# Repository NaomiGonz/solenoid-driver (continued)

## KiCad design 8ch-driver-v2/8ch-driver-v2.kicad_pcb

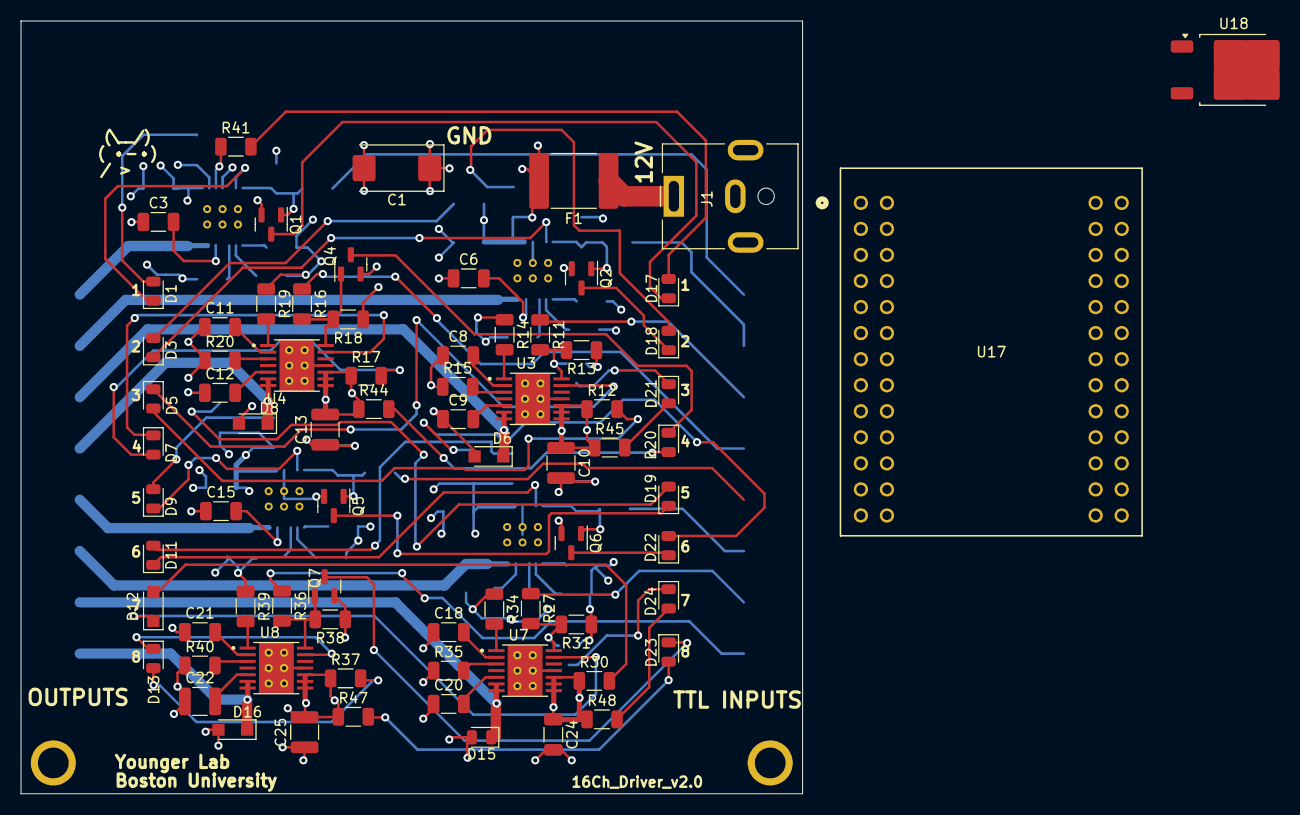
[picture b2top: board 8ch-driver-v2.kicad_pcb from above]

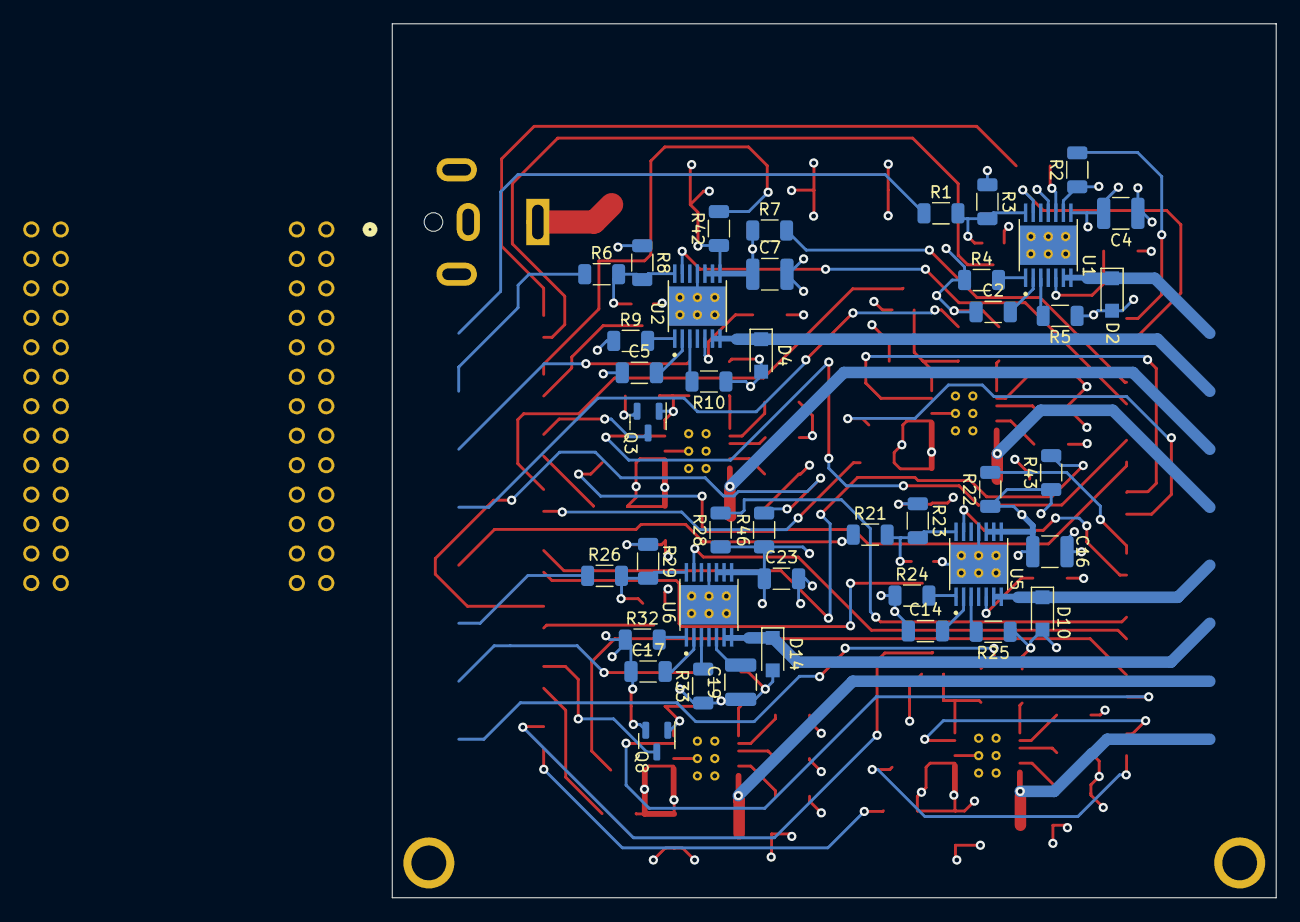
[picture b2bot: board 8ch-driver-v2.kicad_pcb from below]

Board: 4 copper layers, 76.2 x 75.3 mm, 119 parts (42 on the bottom side), 91 nets.

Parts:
C1: 47uF; CP_EIA-7343-43_Kemet-X_Pad2.25x2.55mm_HandSolder
C2, C5, C8, C11, C14, C17, C20, C23: 0.18uF; C_1206_3216Metric
C3, C6, C9, C12, C15, C18, C21, C24: 470pF; C_1206_3216Metric
C4, C7, C10, C13, C16, C19, C22, C25: 10uF; C_1210_3225Metric
D1, D3, D5, D7, D9, D11, D13, D15: LED; LED_0805_2012Metric
D2, D4, D6, D8, D10, D12, D14, D16: PMEG10010ELRX; Nexperia_CFP3_SOD-123W
D17, D18, D19, D20, D21, D22, D23, D24: LED Green; LED_0805_2012Metric
F1: 0ZCF0125FF2C; Fuse_2920_7451Metric
H1, H2: MountingHole; MountingHole_2.2mm_M2_Pad
J1: Barrel_Jack; BarrelJack_CUI_PJ-063AH_Horizontal
Q1, Q2, Q3, Q4, Q5, Q6, Q7, Q8: 2N7002E; SOT-23
R1, R6, R11, R16, R21, R26, R31, R36: 49R9; R_1206_3216Metric
R2, R3, R7, R8, R12, R13, R17, R18, R22, R23, R27, R28, R32, R33, R37, R38: 4k7; R_1206_3216Metric
R4, R9, R14, R19, R24, R29, R34, R39: 162k; R_1206_3216Metric
R5, R10, R15, R20, R25, R30, R35, R40: 191k; R_1206_3216Metric
R41, R42, R43, R44, R45, R46, R47, R48: 10K; R_1206_3216Metric
U1, U2, U3, U4, U5, U6, U7, U8: DRV104PWP; IC_TPS27S100BPWPR
U17: FT4232H MINI MODULE; FT4232H_FTD
U18: BD33FC0FP; TO-252-2

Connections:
+3.3V: U17.CN2-1 (V3V3), U17.CN2-3 (V3V3), U17.CN2-5 (V3V3), U18.3 (VO)
+12V: C1.1, C4.1, C7.1, C10.1, C13.1, C16.1, C19.1, C22.1, C25.1, F1.2, R2.1, R7.1, R12.1, R17.1, R22.1, R27.1, R32.1, R37.1, R41.1, R42.1, R43.1, R44.1, R45.1, R46.1, R47.1, R48.1, U1.8 (VPS2), U1.9 (VPS1), U1.10 (+VS), U2.8 (VPS2), U2.9 (VPS1), U2.10 (+VS), U3.8 (VPS2), U3.9 (VPS1), U3.10 (+VS), U4.8 (VPS2), U4.9 (VPS1), U4.10 (+VS), U5.8 (VPS2), U5.9 (VPS1), U5.10 (+VS), U6.8 (VPS2), U6.9 (VPS1), U6.10 (+VS), U7.8 (VPS2), U7.9 (VPS1), U7.10 (+VS), U8.8 (VPS2), U8.9 (VPS1), U8.10 (+VS), U18.1 (VCC)
/12V_IN: F1.1, J1.1
/additonal-channels-p1/delay3: C8.2, U3.2 (DELAY_ADJ)
/additonal-channels-p1/delay4: C11.2, U4.2 (DELAY_ADJ)
/additonal-channels-p1/delay5: C14.2, U5.2 (DELAY_ADJ)
/additonal-channels-p1/duty3: R14.2, U3.1 (DUTY_CYCLE_ADJ)
/additonal-channels-p1/duty4: R19.2, U4.1 (DUTY_CYCLE_ADJ)
/additonal-channels-p1/duty5: R24.2, U5.1 (DUTY_CYCLE_ADJ)
/additonal-channels-p1/fault3: D5.1 (K), U3.13 (STATUS_OK_FLAG)
/additonal-channels-p1/fault4: D7.1 (K), U4.13 (STATUS_OK_FLAG)
/additonal-channels-p1/fault5: D9.1 (K), U5.13 (STATUS_OK_FLAG)
/additonal-channels-p1/freq3: R15.2, U3.3 (OSC_FREQ_ADJ)
/additonal-channels-p1/freq4: R20.2, U4.3 (OSC_FREQ_ADJ)
/additonal-channels-p1/freq5: R25.2, U5.3 (OSC_FREQ_ADJ)
/additonal-channels-p1/in_term3: Q3.1 (G), R11.2, R13.2, U3.14 (INPUT)
/additonal-channels-p1/in_term4: Q4.1 (G), R16.2, R18.2, U4.14 (INPUT)
/additonal-channels-p1/in_term5: Q5.1 (G), R21.2, R23.2, U5.14 (INPUT)
/additonal-channels-p2/delay6: C17.2, U6.2 (DELAY_ADJ)
/additonal-channels-p2/delay7: C20.2, U7.2 (DELAY_ADJ)
/additonal-channels-p2/delay8: C23.2, U8.2 (DELAY_ADJ)
/additonal-channels-p2/duty6: R29.2, U6.1 (DUTY_CYCLE_ADJ)
/additonal-channels-p2/duty7: R34.2, U7.1 (DUTY_CYCLE_ADJ)
/additonal-channels-p2/duty8: R39.2, U8.1 (DUTY_CYCLE_ADJ)
/additonal-channels-p2/fault6: D11.1 (K), U6.13 (STATUS_OK_FLAG)
/additonal-channels-p2/fault7: D13.1 (K), U7.13 (STATUS_OK_FLAG)
/additonal-channels-p2/fault8: D15.1 (K), U8.13 (STATUS_OK_FLAG)
/additonal-channels-p2/freq6: R30.2, U6.3 (OSC_FREQ_ADJ)
/additonal-channels-p2/freq7: R35.2, U7.3 (OSC_FREQ_ADJ)
/additonal-channels-p2/freq8: R40.2, U8.3 (OSC_FREQ_ADJ)
/additonal-channels-p2/in_term5: R26.2, R28.2, R31.2, R33.2, R36.2, R38.2, U6.14 (INPUT), U7.14 (INPUT), U8.14 (INPUT)
/delay1: C2.2, U1.2 (DELAY_ADJ)
/delay2: C5.2, U2.2 (DELAY_ADJ)
/duty1: R4.2, U1.1 (DUTY_CYCLE_ADJ)
/duty2: R9.2, U2.1 (DUTY_CYCLE_ADJ)
/fault1: D1.1 (K), U1.13 (STATUS_OK_FLAG)
/fault2: D3.1 (K), U2.13 (STATUS_OK_FLAG)
/freq1: R5.2, U1.3 (OSC_FREQ_ADJ)
/freq2: R10.2, U2.3 (OSC_FREQ_ADJ)
/in_term1: Q1.1 (G), R1.2, R3.2, U1.14 (INPUT)
/in_term2: Q2.1 (G), R6.2, R8.2, U2.14 (INPUT)
GND: C1.2, C2.1, C3.1, C4.2, C5.1, C6.1, C7.2, C8.1, C9.1, C10.2, C11.1, C12.1, C13.2, C14.1, C15.1, C16.2, C17.1, C18.1, C19.2, C20.1, C21.1, C22.2, C23.1, C24.1, C25.2, D2.2 (A), D4.2 (A), D6.2 (A), D8.2 (A), D10.2 (A), D12.2 (A), D14.2 (A), D16.2 (A), J1.2, Q1.2 (S), Q2.2 (S), Q3.2 (S), Q4.2 (S), Q5.2 (S), Q6.2 (S), Q7.2 (S), Q8.2 (S), R3.1, R4.1, R5.1, R8.1, R9.1, R10.1, R13.1, R14.1, R15.1, R18.1, R19.1, R20.1, R23.1, R24.1, R25.1, R28.1, R29.1, R30.1, R33.1, R34.1, R35.1, R38.1, R39.1, R40.1, U1.11 (GND), U1.15 (EPAD), U2.11 (GND), U2.15 (EPAD), U3.11 (GND), U3.15 (EPAD), U4.11 (GND), U4.15 (EPAD), U5.11 (GND), U5.15 (EPAD), U6.11 (GND), U6.15 (EPAD), U7.11 (GND), U7.15 (EPAD), U8.11 (GND), U8.15 (EPAD), U17.CN2-2 (GND), U17.CN2-4 (GND), U17.CN2-6 (GND), U18.2 (GND)
unnamed: D1.2 (A), R2.2
unnamed: D3.2 (A), R7.2
unnamed: D5.2 (A), R12.2
unnamed: D7.2 (A), R17.2
unnamed: D9.2 (A), R22.2
unnamed: D11.2 (A), R27.2
unnamed: D13.2 (A), R32.2
unnamed: D15.2 (A), R37.2
unnamed: D17.2 (A), R41.2
unnamed: D17.1 (K), Q1.3 (D)
unnamed: D18.2 (A), R42.2
unnamed: D18.1 (K), Q2.3 (D)
unnamed: D19.2 (A), R43.2
unnamed: D19.1 (K), Q5.3 (D)
unnamed: D20.2 (A), R44.2
unnamed: D20.1 (K), Q4.3 (D)
unnamed: D21.2 (A), R45.2
unnamed: D21.1 (K), Q3.3 (D)
unnamed: D22.2 (A), R46.2
unnamed: D22.1 (K), Q6.3 (D)
unnamed: D23.2 (A), R47.2
unnamed: D23.1 (K), Q8.3 (D)
unnamed: D24.2 (A), R48.2
unnamed: D24.1 (K), Q7.3 (D)
unnamed: C3.2, U1.5 (BOOT)
unnamed: C6.2, U2.5 (BOOT)
unnamed: C9.2, U3.5 (BOOT)
unnamed: C12.2, U4.5 (BOOT)
unnamed: C15.2, U5.5 (BOOT)
unnamed: C18.2, U6.5 (BOOT)
unnamed: C21.2, U7.5 (BOOT)
unnamed: C24.2, U8.5 (BOOT)
unnamed: U17.CN3-1 (VBUS), U17.CN3-3 (VCC)
Relay01: R1.1, U17.CN2-7 (AD0)
Relay02: R6.1, U17.CN2-10 (AD1)
Relay03: R11.1, U17.CN2-9 (AD2)
Relay04: R16.1, U17.CN2-12 (AD3)
Relay05: R21.1, U17.CN2-14 (AD4)
Relay06: R26.1, U17.CN2-13 (AD5)
Relay07: R31.1, U17.CN2-16 (AD6)
Relay08: R36.1, U17.CN2-15 (AD7)
out01: D2.1 (K), U1.6 (OUT1), U1.7 (OUT2)
out02: D4.1 (K), U2.6 (OUT1), U2.7 (OUT2)
out03: D6.1 (K), U3.6 (OUT1), U3.7 (OUT2)
out04: D8.1 (K), U4.6 (OUT1), U4.7 (OUT2)
out05: D10.1 (K), U5.6 (OUT1), U5.7 (OUT2)
out06: D12.1 (K), U6.6 (OUT1), U6.7 (OUT2)
out07: D14.1 (K), U7.6 (OUT1), U7.7 (OUT2)
out08: D16.1 (K), U8.6 (OUT1), U8.7 (OUT2)

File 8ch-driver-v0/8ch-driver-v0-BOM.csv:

Source:,/Users/naomi_12/Desktop/Meg-Younger-Lab/solenoid-driver-master/8ch-driver-v0/8ch-driver-v0.kicad_sch,,,,,,,,,,
Date:,"2023 September 01, Friday 14:24:09",,,,,,,,,,
Tool:,Eeschema 7.0.7,,,,,,,,,,
Generator:,/Applications/KiCad/KiCad.app/Contents/SharedSupport/plugins/bom_csv_grouped_by_value.py,,,,,,,,,,
Component Count:,120,,,,,,,,,,
,,,,,,,,,,,
Collated Components:,,,,,,,,,,,
,,,,,,,,,,,
Item,Qty,Reference(s),Value,LibPart,Footprint,Link to Buy,Mfg,PartNum,Qty to Order,Indv Price,Group Price
1,1,C1,47uF,Device:C_Polarized,Capacitor_Tantalum_SMD:CP_EIA-7343-43_Kemet-X_Pad2.25x2.55mm_HandSolder,https://www.digikey.com/en/products/detail/kemet/T491X476K03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,Kemet,T491X476K035AT,10,$2.33 ,$23.28 
2,8,"C2, C5, C8, C11, C14, C17, C18, C21",0.18uF,Device:C_Small,Capacitor_SMD:C_0805_2012Metric,https://www.digikey.com/en/products/detail/kyocera-avx/08053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,KYOCERA AVX,08053C184KAT2A,50,$0.14 ,$4.32 
3,8,"C3, C6, C9, C12, C15, C19, C20, C22",470pF,Device:C_Small,Capacitor_SMD:C_0805_2012Metric,https://www.digikey.com/en/products/detail/kemet/C0805C471K5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,Kemet,C0805C471K5RAC7800,50,$0.04 ,$1.87 
4,8,"C4, C7, C10, C13, C16, C23, C24, C25",10uF,Device:C,Capacitor_SMD:C_1210_3225Metric,https://www.digikey.com/en/products/detail/samsung-electro-m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,Samsung Electro-Mechanics,CL32A106KLULNNE,50,$0.17 ,$8.49 
5,8,"D1, D3, D5, D7, D9, D11, D12, D13, D17, D18, D19, D20, D21, D22, D23, D24",LED Red,Device:LED,LED_SMD:LED_0805_2012Metric,https://www.digikey.com/en/products/detail/wrth-elektronik/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,Wurth,150080RS75000,50,$0.18 ,$8.80 
6,8,"D2, D4, D6, D8, D10, D14, D15, D16",LED Green,Device:D,LED_SMD:LED_0805_2012Metric,https://www.digikey.com/en/products/detail/wrth-elektronik/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,Wurth,150080VS75000,50,$0.18 ,$8.80 
7,8,"D2, D4, D6, D8, D10, D14, D15, D16",PMEG10010ELRX,Device:D,Diode_SMD:Nexperia_CFP3_SOD-123W,https://www.digikey.com/en/products/detail/nexperia-usa-inc/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,Nexperia,PMEG10010ELRX,50,$0.29 ,$14.30 
8,1,F1,0ZCF0125FF2C,Device:Polyfuse,Fuse:Fuse_2920_7451Metric,https://www.digikey.com/en/products/detail/bel-fuse-inc/0ZCF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,Bel Fuse,0ZCF0125FF2C,10,$0.28 ,$2.84 
9,1,J1,Barrel_Jack,Connector:Barrel_Jack,Connector_BarrelJack:BarrelJack_CUI_PJ-063AH_Horizontal,https://www.digikey.com/en/products/detail/cui-devices/PJ-06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,CUI,PJ-063AH,~,~,~
10,2,"J2, J3",Screw_Terminal_01x08,Connector:Screw_Terminal_01x08,"TerminalBlock_Phoenix:TerminalBlock_Phoenix_PT-1,5-8-5.0-H_1x08_P5.00mm_Horizontal",https://www.digikey.com/en/products/detail/cui-devices/PJ-06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,Phoenix Contact,1935226,15,$1.97 ,$29.54 
11,1,J4,Screw_Terminal_01x14,Connector:Screw_Terminal_01x14,"TerminalBlock_Phoenix:TerminalBlock_Phoenix_PT-1,5-14-5.0-H_1x14_P5.00mm_Horizontal",https://www.digikey.com/en/products/detail/phoenix-contact/1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,Phoenix Contact,1935284,10,$3.40 ,$34.03 
12,8,"Q1, Q2, Q3, Q4, Q5, Q6, Q7, Q8",2N7002E,Transistor_FET:2N7002E,Package_TO_SOT_SMD:SOT-23,https://www.digikey.com/en/products/detail/diodes-incorporat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,Diodes Inc,ZXMN2B01FTA,50,$0.37 ,$18.70 
13,8,"R1, R6, R11, R16, R21, R26, R27, R36",49R9,Device:R_US,Resistor_SMD:R_0805_2012Metric,https://www.digikey.com/en/products/detail/yageo/RC0805FR-07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,Yageo,RC0805FR-0749R9L,50,$0.02 ,$0.76 
14,16,"R2, R3, R7, R8, R12, R13, R17, R18, R22, R23, R28, R29, R30, R31, R37, R38",4k7,Device:R_US,Resistor_SMD:R_0805_2012Metric,https://www.digikey.com/en/products/detail/yageo/RC0805JR-07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,Yageo,RC0805JR-074K7L,100,$0.01 ,$1.14 
15,8,"R4, R9, R14, R19, R24, R32, R34, R39",162k,Device:R_US,Resistor_SMD:R_0805_2012Metric,https://www.digikey.com/en/products/detail/yageo/RC0805FR-07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,Yageo,RC0805FR-07162KL,50,$0.02 ,$0.76 
16,8,"R5, R10, R15, R20, R25, R33, R35, R40",191k,Device:R_US,Resistor_SMD:R_0805_2012Metric,https://www.digikey.com/en/products/detail/yageo/RC0805FR-07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,Yageo,RC0805FR-07191KL,50,$0.02 ,$0.77 
17,8,"R41, R42, R43, R44, R45, R46, R47, R48",1K,Device:R_US,Resistor_SMD:R_0805_2012Metric,https://www.digikey.com/en/products/detail/yageo/RC0805FR-07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,Yageo,RC0805FR-071KL,50,$0.02 ,$0.76 
18,8,"U1, U2, U3, U4, U5, U6, U7, U8",DRV104PWP,DRV104PWP:DRV104PWP,Solenoid_Driver:IC_TPS27S100BPWPR,https://www.digikey.com/en/products/detail/texas-instruments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,TI,DRV104PWP,50,$4.55 ,$227.48 
,,,,,,,,,,TOTAL:,$386.64 
,Digikey Cart:,https://www.digikey.com/ordering/shoppingcart,,,,,,,,,

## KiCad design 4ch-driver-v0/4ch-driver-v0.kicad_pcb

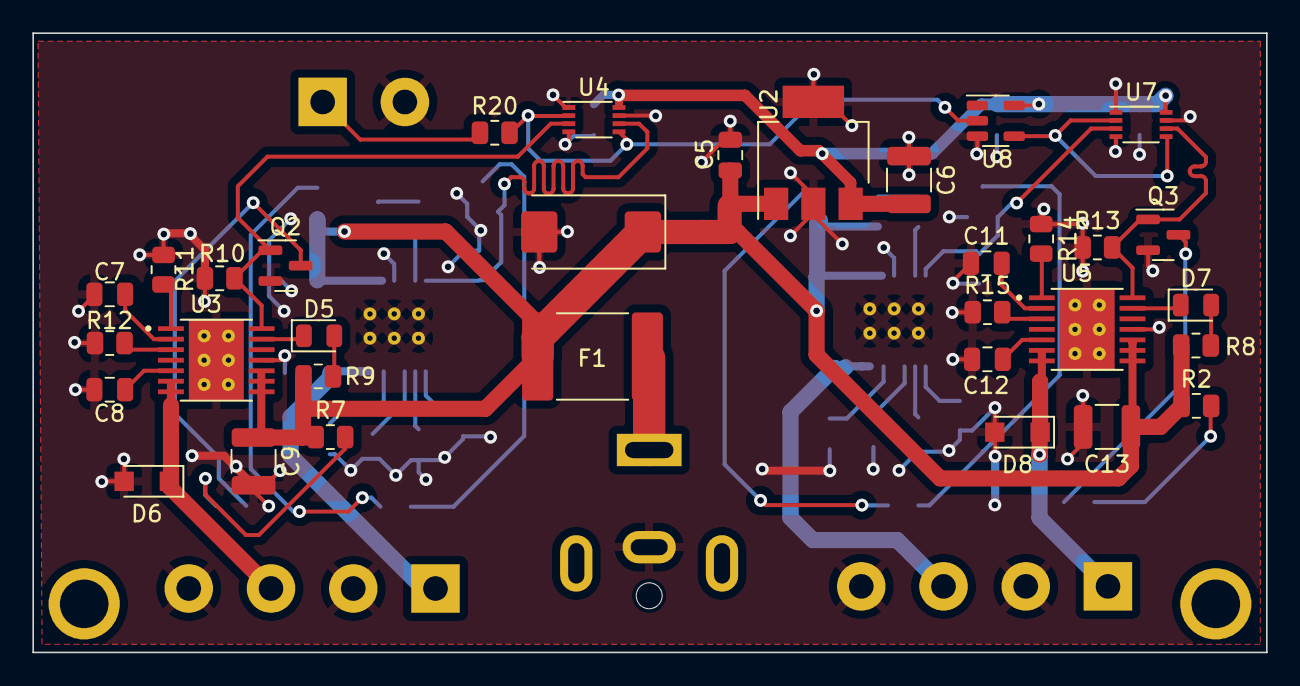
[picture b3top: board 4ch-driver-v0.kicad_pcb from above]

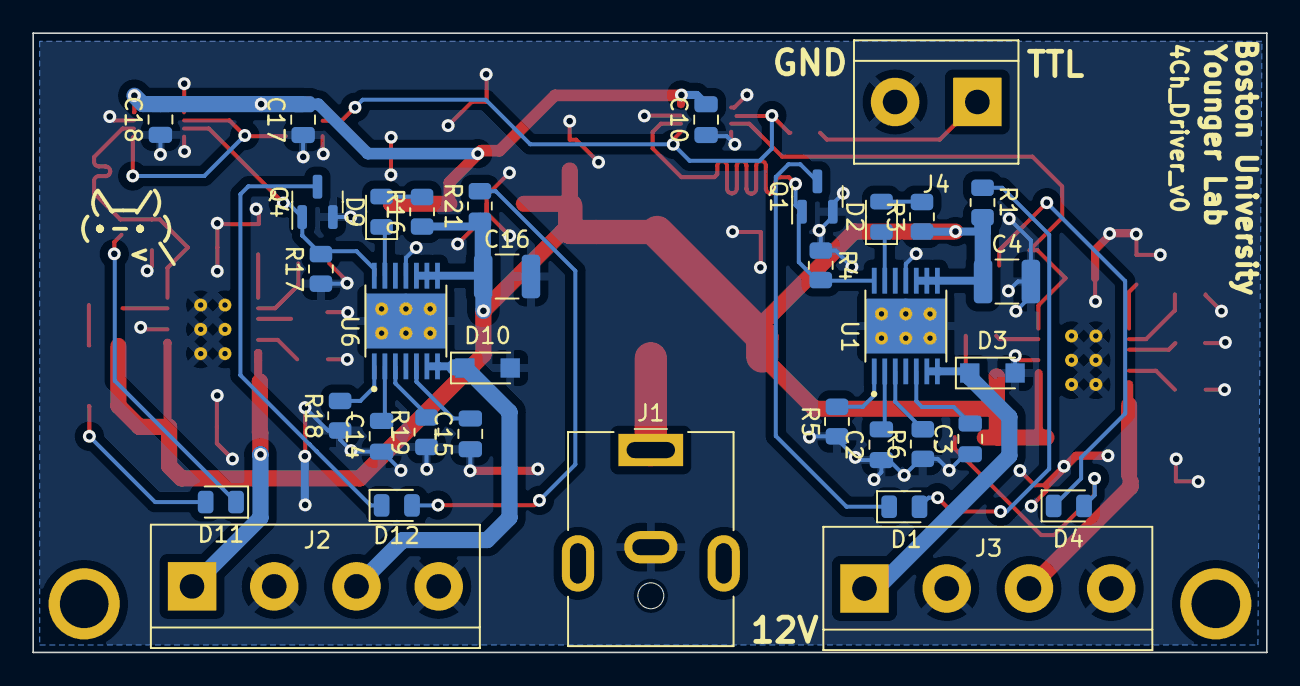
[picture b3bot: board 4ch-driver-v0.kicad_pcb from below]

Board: 2 copper layers, 76.2 x 38.2 mm, 70 parts (35 on the bottom side), 47 nets.

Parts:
C1: 47uF; CP_EIA-7343-43_Kemet-X_Pad2.25x2.55mm_HandSolder
C2, C7, C11, C14: 0.18uF; C_0805_2012Metric
C3, C8, C12, C15: 470pF; C_0805_2012Metric
C4, C6, C9, C13, C16: 10uF; C_1210_3225Metric
C5, C10, C17, C18: 0.1uF; C_0805_2012Metric
D1, D2, D4, D5, D7, D9, D11, D12: LED; LED_0805_2012Metric
D3, D6, D8, D10: PMEG10010ELRX; Nexperia_CFP3_SOD-123W
F1: 0ZCF0125FF2C; Fuse_2920_7451Metric
H1, H2: MountingHole; MountingHole_2.2mm_M2_Pad
J1: Barrel_Jack; BarrelJack_CUI_PJ-063AH_Horizontal
J2, J3: Screw_Terminal_01x04; TerminalBlock_bornier-4_P5.08mm
J4: Screw_Terminal_01x02; TerminalBlock_bornier-2_P5.08mm
Q1, Q2, Q3, Q4: 2N7002E; SOT-23
R1, R2, R7, R21: 1K; R_0805_2012Metric
R3, R4, R8, R9, R10, R13, R16, R17: 4k7; R_0805_2012Metric
R5, R11, R14, R18: 162k; R_0805_2012Metric
R6, R12, R15, R19: 191k; R_0805_2012Metric
R20: 49R9; R_0805_2012Metric
U1, U3, U5, U6: DRV104PWP; IC_TPS27S100BPWPR
U2: BD750L2FP3-CE2; SOT-223-3_TabPin2
U4, U7: SN74LVC2G125DCUR; VSSOP-8_2.3x2mm_P0.5mm
U8: SN74AHCT1G04DBVR; SOT-23-5

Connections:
+5V: C6.2, C10.2, C17.2, C18.2, U2.3 (Vout), U4.8 (Vcc), U7.8 (Vcc), U8.5 (Vcc)
+12V: C1.1, C4.1, C5.2, C9.1, C13.1, C16.1, F1.2, R1.1, R2.1, R3.1, R7.1, R8.1, R9.1, R16.1, R21.1, U1.8 (VPS2), U1.9 (VPS1), U1.10 (+VS), U2.1 (Vcc), U3.8 (VPS2), U3.9 (VPS1), U3.10 (+VS), U5.8 (VPS2), U5.9 (VPS1), U5.10 (+VS), U6.8 (VPS2), U6.9 (VPS1), U6.10 (+VS)
/12V_IN: F1.1, J1.1
/delay1: C2.2, U1.2 (DELAY_ADJ)
/delay2: C7.2, U3.2 (DELAY_ADJ)
/duty1: R5.2, U1.1 (DUTY_CYCLE_ADJ)
/duty2: R11.2, U3.1 (DUTY_CYCLE_ADJ)
/fault1: D2.1 (K), U1.13 (STATUS_OK_FLAG)
/fault2: D5.1 (K), U3.13 (STATUS_OK_FLAG)
/freq1: R6.2, U1.3 (OSC_FREQ_ADJ)
/freq2: R12.2, U3.3 (OSC_FREQ_ADJ)
/in: J4.1, R20.1
/in_term1: Q1.1 (G), R4.2, U1.14 (INPUT), U4.6 (1Y)
/in_term2: Q2.1 (G), R10.2, U3.14 (INPUT), U4.3 (2Y)
/inverted_signal/delay3: C11.2, U5.2 (DELAY_ADJ)
/inverted_signal/delay4: C14.2, U6.2 (DELAY_ADJ)
/inverted_signal/duty3: R14.2, U5.1 (DUTY_CYCLE_ADJ)
/inverted_signal/duty4: R18.2, U6.1 (DUTY_CYCLE_ADJ)
/inverted_signal/fault3: D7.1 (K), U5.13 (STATUS_OK_FLAG)
/inverted_signal/fault4: D9.1 (K), U6.13 (STATUS_OK_FLAG)
/inverted_signal/freq3: R15.2, U5.3 (OSC_FREQ_ADJ)
/inverted_signal/freq4: R19.2, U6.3 (OSC_FREQ_ADJ)
/inverted_signal/in_term3: Q3.1 (G), R13.2, U5.14 (INPUT), U7.6 (1Y)
/inverted_signal/in_term4: Q4.1 (G), R17.2, U6.14 (INPUT), U7.3 (2Y)
/inverted_signal/inverted: U7.2 (1A), U7.5 (2A), U8.4 (Out)
/inverted_signal/out3: D8.1 (K), J2.1, U5.6 (OUT1), U5.7 (OUT2)
/inverted_signal/out4: D10.1 (K), J2.3, U6.6 (OUT1), U6.7 (OUT2)
/out1: D3.1 (K), J3.1, U1.6 (OUT1), U1.7 (OUT2)
/out2: D6.1 (K), J3.3, U3.6 (OUT1), U3.7 (OUT2)
GND: C1.2, C2.1, C3.1, C4.2, C5.1, C6.1, C7.1, C8.1, C9.2, C10.1, C11.1, C12.1, C13.2, C14.1, C15.1, C16.2, C17.1, C18.1, D3.2 (A), D6.2 (A), D8.2 (A), D10.2 (A), J1.2, J2.2, J2.4, J3.2, J3.4, J4.2, Q1.2 (S), Q2.2 (S), Q3.2 (S), Q4.2 (S), R4.1, R5.1, R6.1, R10.1, R11.1, R12.1, R13.1, R14.1, R15.1, R17.1, R18.1, R19.1, U1.11 (GND), U1.15 (EPAD), U1.16, U1.17, U1.18, U1.19, U1.20, U1.21, U2.2 (GND), U3.11 (GND), U3.15 (EPAD), U3.16, U3.17, U3.18, U3.19, U3.20, U3.21, U4.1 (1~OE), U4.4 (GND), U4.7 (2~OE), U5.11 (GND), U5.15 (EPAD), U5.16, U5.17, U5.18, U5.19, U5.20, U5.21, U6.11 (GND), U6.15 (EPAD), U6.16, U6.17, U6.18, U6.19, U6.20, U6.21, U7.1 (1~OE), U7.4 (GND), U7.7 (2~OE), U8.3 (GND)
unnamed: D1.2 (A), R1.2
unnamed: D1.1 (K), Q1.3 (D)
unnamed: D2.2 (A), R3.2
unnamed: D4.2 (A), R7.2
unnamed: D4.1 (K), Q2.3 (D)
unnamed: D5.2 (A), R9.2
unnamed: D7.2 (A), R8.2
unnamed: D9.2 (A), R16.2
unnamed: D11.2 (A), R2.2
unnamed: D11.1 (K), Q3.3 (D)
unnamed: D12.2 (A), R21.2
unnamed: D12.1 (K), Q4.3 (D)
unnamed: C3.2, U1.5 (BOOT)
unnamed: C8.2, U3.5 (BOOT)
unnamed: C12.2, U5.5 (BOOT)
unnamed: C15.2, U6.5 (BOOT)
in_sig: R20.2, U4.2 (1A), U4.5 (2A), U8.2 (In)

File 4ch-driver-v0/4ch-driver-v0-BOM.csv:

"Source:","/Users/naomi_12/Desktop/Research/Younger-Lab/solenoid-driver-master/4ch-driver-v0/4ch-driver-v0.kicad_sch"
"Date:","2024 March 31, Sunday 21:11:15"
"Tool:","Eeschema 7.0.7"
"Generator:","/Applications/KiCad/KiCad.app/Contents/SharedSupport/plugins/bom_csv_grouped_by_value.py"
"Component Count:","68"

"Collated Components:"

"Item","Qty","Reference(s)","Value","LibPart","Footprint","Datasheet","DNP","Mfg","PartNum","Sim.Device","Sim.Pins"
"1","1","C1","47uF","Device:C_Polarized","Capacitor_Tantalum_SMD:CP_EIA-7343-43_Kemet-X_Pad2.25x2.55mm_HandSolder","~","","Kemet","T491X476K035AT","",""
"2","4","C2, C7, C11, C14","0.18uF","Device:C_Small","Capacitor_SMD:C_0805_2012Metric","~","","KYOCERA AVX","08053C184KAT2A","",""
"3","4","C3, C8, C12, C15","470pF","Device:C_Small","Capacitor_SMD:C_0805_2012Metric","~","","Kemet","C0805C471K5RAC7800","",""
"4","4","C4, C9, C13, C16","10uF","Device:C","Capacitor_SMD:C_1210_3225Metric","~","","Samsung Electro-Mechanics","CL32A106KLULNNE","",""
"5","4","C5, C10, C17, C18","0.1uF","Device:C_Small","Capacitor_SMD:C_0805_2012Metric","~","","KYOCERA AVX","08053C184KAT2A","",""
"6","1","C6","10uF","Device:C_Small","Capacitor_SMD:C_1210_3225Metric","~","","KYOCERA AVX","08053C184KAT2A","",""
"7","8","D1, D2, D4, D5, D7, D9, D11, D12","LED","Device:LED","LED_SMD:LED_0805_2012Metric","~","","Wurth","150080RS75000","",""
"8","4","D3, D6, D8, D10","PMEG10010ELRX","Device:D","Diode_SMD:Nexperia_CFP3_SOD-123W","~","","Nexperia","PMEG10010ELRX","D","1=K 2=A"
"9","1","F1","0ZCF0125FF2C","Device:Polyfuse","Fuse:Fuse_2920_7451Metric","~","","Bel Fuse","0ZCF0125FF2C","",""
"10","1","J1","Barrel_Jack","Connector:Barrel_Jack","Connector_BarrelJack:BarrelJack_CUI_PJ-063AH_Horizontal","~","","CUI","PJ-063AH","",""
"11","2","J2, J3","Screw_Terminal_01x04","Connector:Screw_Terminal_01x04","TerminalBlock:TerminalBlock_bornier-4_P5.08mm","~","","","","",""
"12","1","J4","Screw_Terminal_01x02","Connector:Screw_Terminal_01x02","TerminalBlock:TerminalBlock_bornier-2_P5.08mm","~","","TE","282837-2","",""
"13","4","Q1, Q2, Q3, Q4","2N7002E","Transistor_FET:2N7002E","Package_TO_SOT_SMD:SOT-23","http://www.diodes.com/assets/Datasheets/ds30376.pdf","","","","",""
"14","4","R1, R2, R7, R21","1K","Device:R_US","Resistor_SMD:R_0805_2012Metric","~","","Yageo","RC0805FR-07162KL","",""
"15","8","R3, R4, R8, R9, R10, R13, R16, R17","4k7","Device:R_US","Resistor_SMD:R_0805_2012Metric","~","","Yageo","RC0805JR-074K7L","",""
"16","4","R5, R11, R14, R18","162k","Device:R_US","Resistor_SMD:R_0805_2012Metric","~","","Yageo","RC0805FR-07162KL","",""
"17","4","R6, R12, R15, R19","191k","Device:R_US","Resistor_SMD:R_0805_2012Metric","~","","Yageo","RC0805FR-07191KL","",""
"18","1","R20","49R9","Device:R_US","Resistor_SMD:R_0805_2012Metric","~","","Yageo","RC0805FR-0749R9L","",""
"19","4","U1, U3, U5, U6","DRV104PWP","DRV104PWP:DRV104PWP","Solenoid_Driver:IC_TPS27S100BPWPR","","","TI","DRV104PWP","",""
"20","1","U2","BD750L2FP3-CE2","Regulator_Linear:BD750L2FP3-CE","Package_TO_SOT_SMD:SOT-223-3_TabPin2","","","","","",""
"21","2","U4, U7","SN74LVC2G125DCUR","Buffer:SN74LVC2G125","Package_SO:VSSOP-8_2.3x2mm_P0.5mm","","","","","",""
"22","1","U8","SN74AHCT1G04DBVR","Inverters:SN74AHCT1G04","Package_TO_SOT_SMD:SOT-23-5","","","","","",""

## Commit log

2023-09-02 creation of 8ch-v0 and 2ch-v0
2023-12-13 Revised Board
2024-04-01 Added design files for 4-ch opposing dir board
2024-04-01 fixed screw terminal side
2024-06-06 Cleaning up the protoboard
    Moving away from screw terminals in V2.
2024-06-13 added 8 more channels and an FTDH chip
2024-07-09 progress
2024-07-12 mucho mas progresso
2024-07-25 push
2024-08-05 Ready for 16 chan layout
2024-08-26 test
2024-08-26 16-valve PCB layout for inspection
2024-08-27 Gerber File Creation
2024-09-04 Larger Board and DRC Cleanup
2024-09-04 Clean DRC!!
2024-09-04 Cleaning
2024-09-11 Final Files for Production
2024-10-06 zipped for pcbfab
2024-10-30 notes
